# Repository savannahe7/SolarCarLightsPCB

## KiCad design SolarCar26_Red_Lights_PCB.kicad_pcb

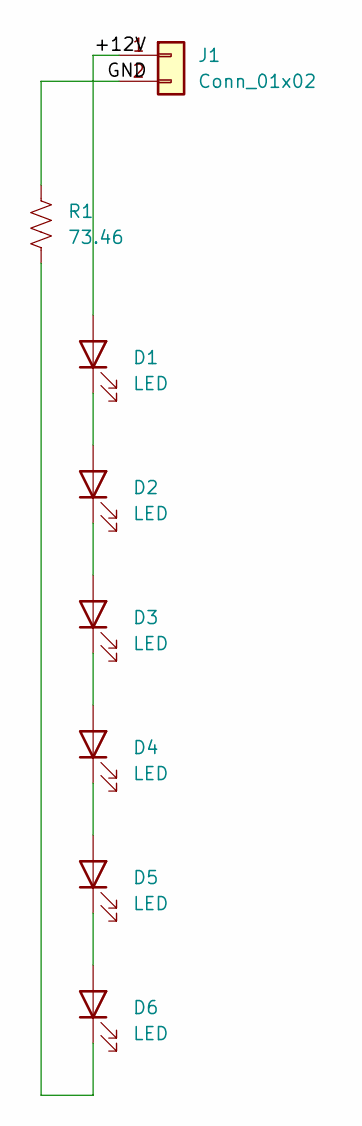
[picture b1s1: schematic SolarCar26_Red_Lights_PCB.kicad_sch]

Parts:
D1, D2, D3, D4, D5, D6: LED; SYNIOS S2222
J1: Conn_01x02; CONN_B02B-WPJSS-1_JST
R1: 73.46; R_0805_2012Metric

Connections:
/+12V: D1.2 (A), J1.1
/GND: J1.2, R1.1
unnamed: D1.1 (K), D2.2 (A)
unnamed: D2.1 (K), D3.2 (A)
unnamed: D3.1 (K), D4.2 (A)
unnamed: D4.1 (K), D5.2 (A)
unnamed: D5.1 (K), D6.2 (A)
unnamed: D6.1 (K), R1.2

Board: 2 copper layers, 8 parts (1 on the bottom side), 8 nets, no tracks yet.
